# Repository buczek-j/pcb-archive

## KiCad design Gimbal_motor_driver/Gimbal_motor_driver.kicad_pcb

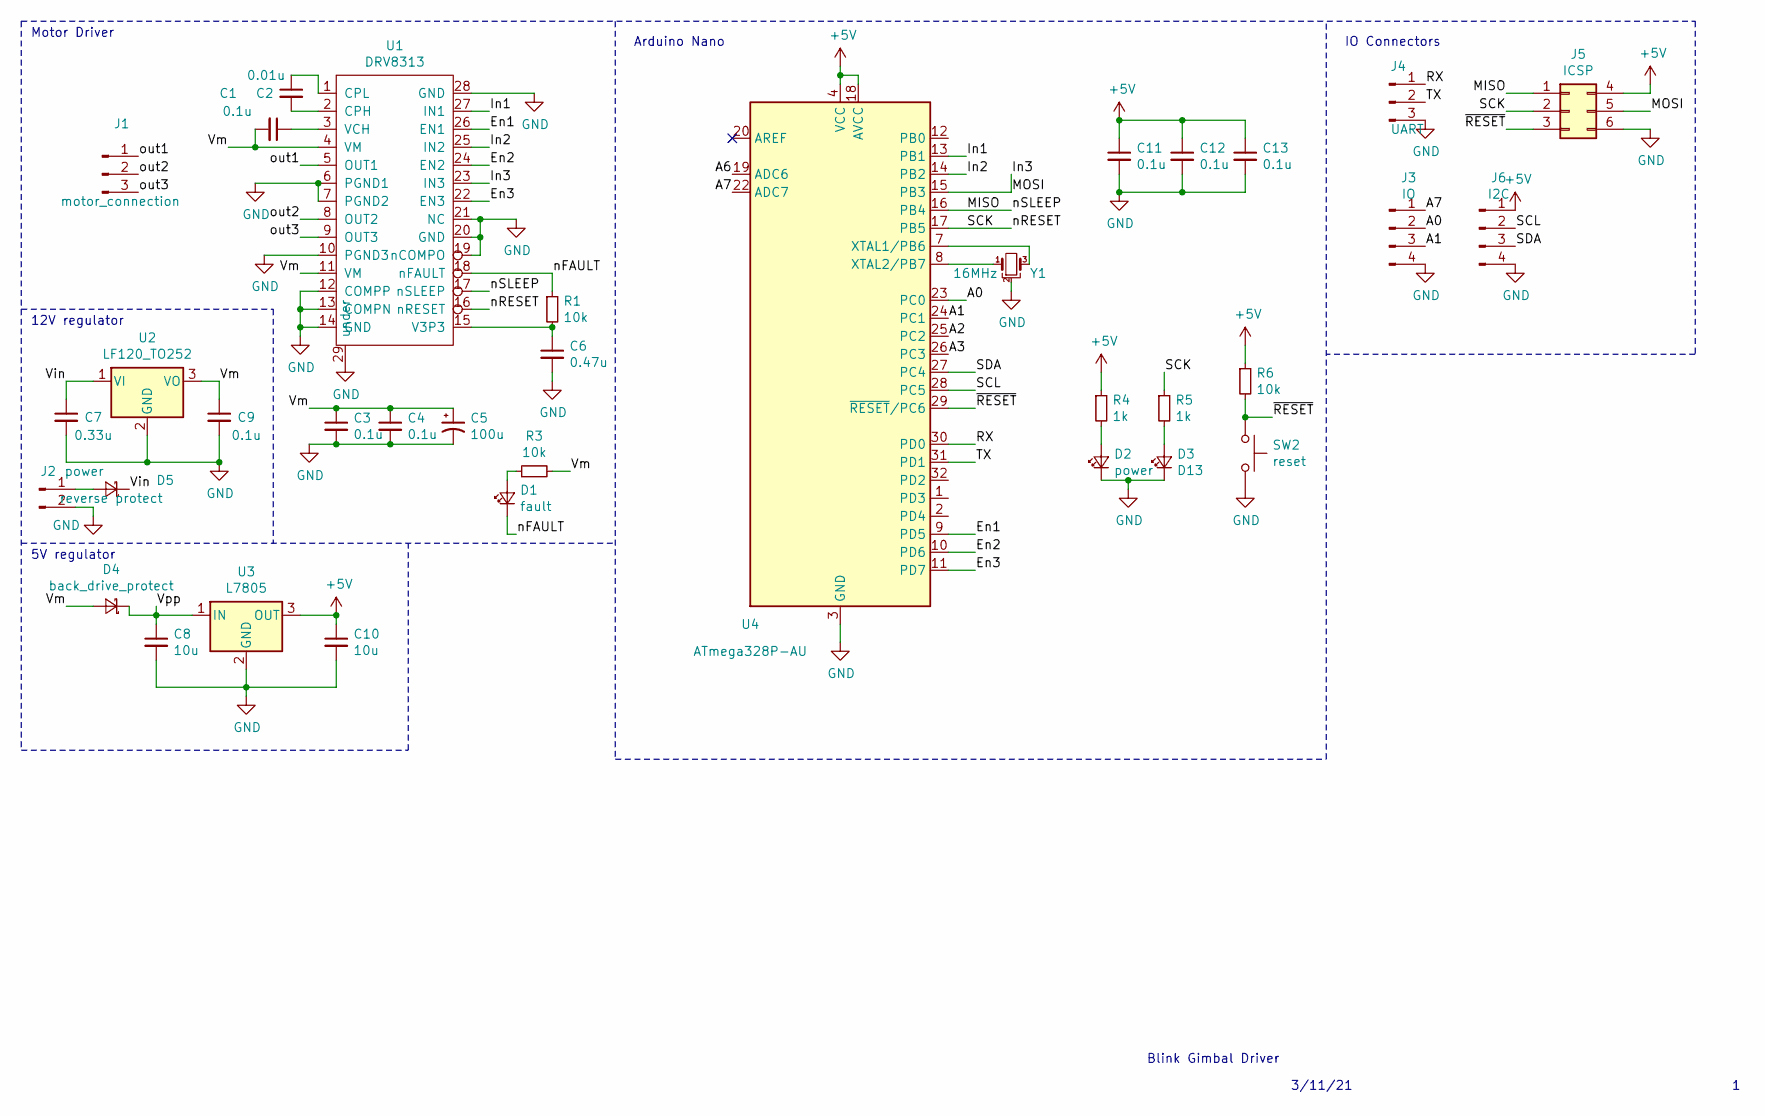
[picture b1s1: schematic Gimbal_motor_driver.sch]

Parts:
C1, C3, C4, C9, C11, C12, C13: 0.1u; C_0402_1005Metric
C2: 0.01u; C_0402_1005Metric
C5: 100u; C_1206_3216Metric_Pad1.42x1.75mm_HandSolder
C6: 0.47u; C_0402_1005Metric
C7: 0.33u; C_0402_1005Metric
C8, C10: 10u; C_0402_1005Metric
D1: fault; LED_0402_1005Metric
D2: power; LED_0402_1005Metric
D3: D13; LED_0402_1005Metric
D4: back_drive_protect; D_SOD-123
D5: reverse protect; D_SMB
J1: motor_connection; PinSocket_1x03_P2.54mm_Vertical
J2: power; PinHeader_1x02_P2.54mm_Vertical
J3: IO; PinHeader_1x04_P2.54mm_Vertical
J4: UART; PinSocket_1x03_P2.54mm_Vertical
J5: ICSP; PinHeader_2x03_P2.54mm_Vertical
J6: I2C; PinHeader_1x04_P2.54mm_Vertical
R1, R3, R6: 10k; R_0402_1005Metric
R4, R5: 1k; R_0402_1005Metric
SW2: reset; PinHeader_1x02_P1.27mm_Vertical
U1: DRV8313; HTSSOP-28-1EP_4.4x9.7mm_P0.65mm_EP2.85x5.4mm_ThermalVias
U2: LF120_TO252; TO-252-2
U3: L7805; SOT-223-3_TabPin2
U4: ATmega328P-AU; TQFP-32_7x7mm_P0.8mm
Y1: 16MHz; Resonator_SMD_muRata_CSTxExxV-3Pin_3.0x1.1mm

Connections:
+5V: C10.1, C11.1, C12.1, C13.1, J5.4, J6.1, R4.1, R6.1, U3.3 (OUT), U4.4 (VCC), U4.6 (VCC), U4.18 (AVCC)
/A0: J3.2, U4.23 (PC0)
/A1: J3.3, U4.24 (PC1)
/A2: U4.25 (PC2)
/A3: U4.26 (PC3)
/A6: U4.19 (ADC6)
/A7: J3.1, U4.22 (ADC7)
/En1: U1.26 (EN1), U4.9 (PD5)
/En2: U1.24 (EN2), U4.10 (PD6)
/En3: U1.22 (EN3), U4.11 (PD7)
/In1: U1.27 (IN1), U4.13 (PB1)
/In2: U1.25 (IN2), U4.14 (PB2)
/In3: J5.5, U1.23 (IN3), U4.15 (PB3)
/MISO: J5.1, U1.17 (nSLEEP), U4.16 (PB4)
/RX: J4.1, U4.30 (PD0)
/SCK: J5.2, R5.1, U1.16 (nRESET), U4.17 (PB5)
/SCL: J6.2, U4.28 (PC5)
/SDA: J6.3, U4.27 (PC4)
/TX: J4.2, U4.31 (PD1)
/Vin: C7.1, D5.1 (K), U2.1 (VI)
/Vm: C1.2, C3.1, C4.1, C5.1, C9.1, D4.2 (A), R3.2, U1.4 (VM), U1.11 (VM), U2.3 (VO)
/Vpp: C8.1, D4.1 (K), U3.1 (IN)
/nFAULT: D1.1 (K), R1.1, U1.18 (nFAULT)
/out1: J1.1, U1.5 (OUT1)
/out2: J1.2, U1.8 (OUT2)
/out3: J1.3, U1.9 (OUT3)
/~RESET: J5.3, R6.2, SW2.1, U4.29 (~RESET~/PC6)
GND: C3.2, C4.2, C5.2, C6.2, C7.2, C8.2, C9.2, C10.2, C11.2, C12.2, C13.2, D2.1 (K), D3.1 (K), J2.2, J3.4, J4.3, J5.6, J6.4, SW2.2, U1.6 (PGND1), U1.7 (PGND2), U1.10 (PGND3), U1.12 (COMPP), U1.13 (COMPN), U1.14 (GND), U1.19 (nCOMPO), U1.20 (GND), U1.21 (NC), U1.28 (GND), U1.29 (under), U2.2 (GND), U3.2 (GND), U4.3 (GND), U4.5 (GND), U4.21 (GND), Y1.2
unnamed: C1.1, U1.3 (VCH)
unnamed: C2.1, U1.1 (CPL)
unnamed: C2.2, U1.2 (CPH)
unnamed: C6.1, R1.2, U1.15 (V3P3)
unnamed: D1.2 (A), R3.1
unnamed: D2.2 (A), R4.2
unnamed: D3.2 (A), R5.2
unnamed: D5.2 (A), J2.1
unnamed: U4.7 (XTAL1/PB6), Y1.3
unnamed: U4.8 (XTAL2/PB7), Y1.1

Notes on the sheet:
Motor Driver
12V regulator
5V regulator
Arduino Nano
IO Connectors
Blink Gimbal Driver
3/11/21

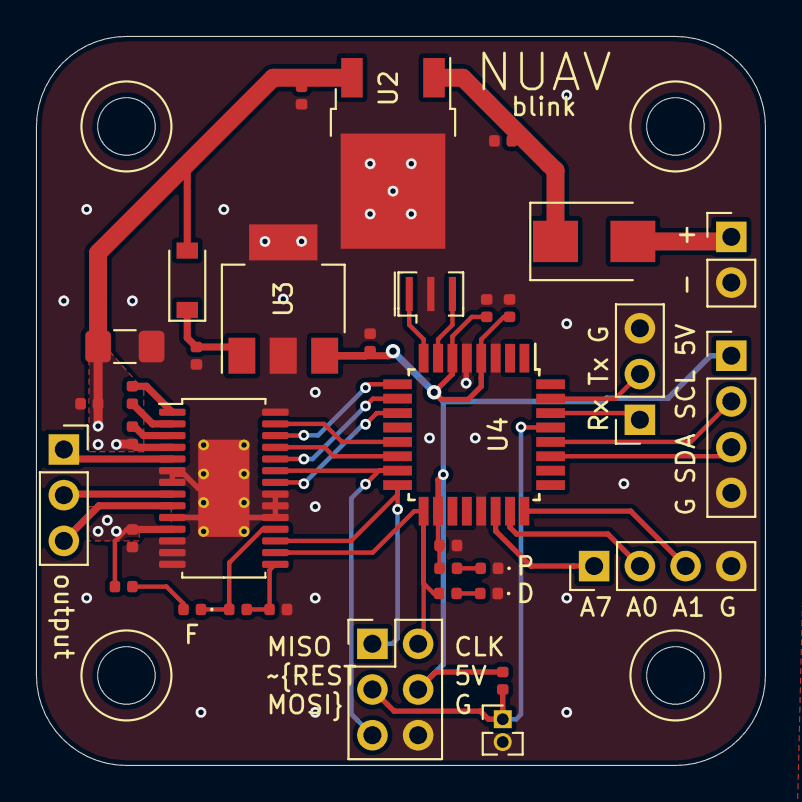
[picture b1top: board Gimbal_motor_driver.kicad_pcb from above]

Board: 2 copper layers, 40.5 x 40.5 mm, 35 parts (0 on the bottom side), 35 nets.

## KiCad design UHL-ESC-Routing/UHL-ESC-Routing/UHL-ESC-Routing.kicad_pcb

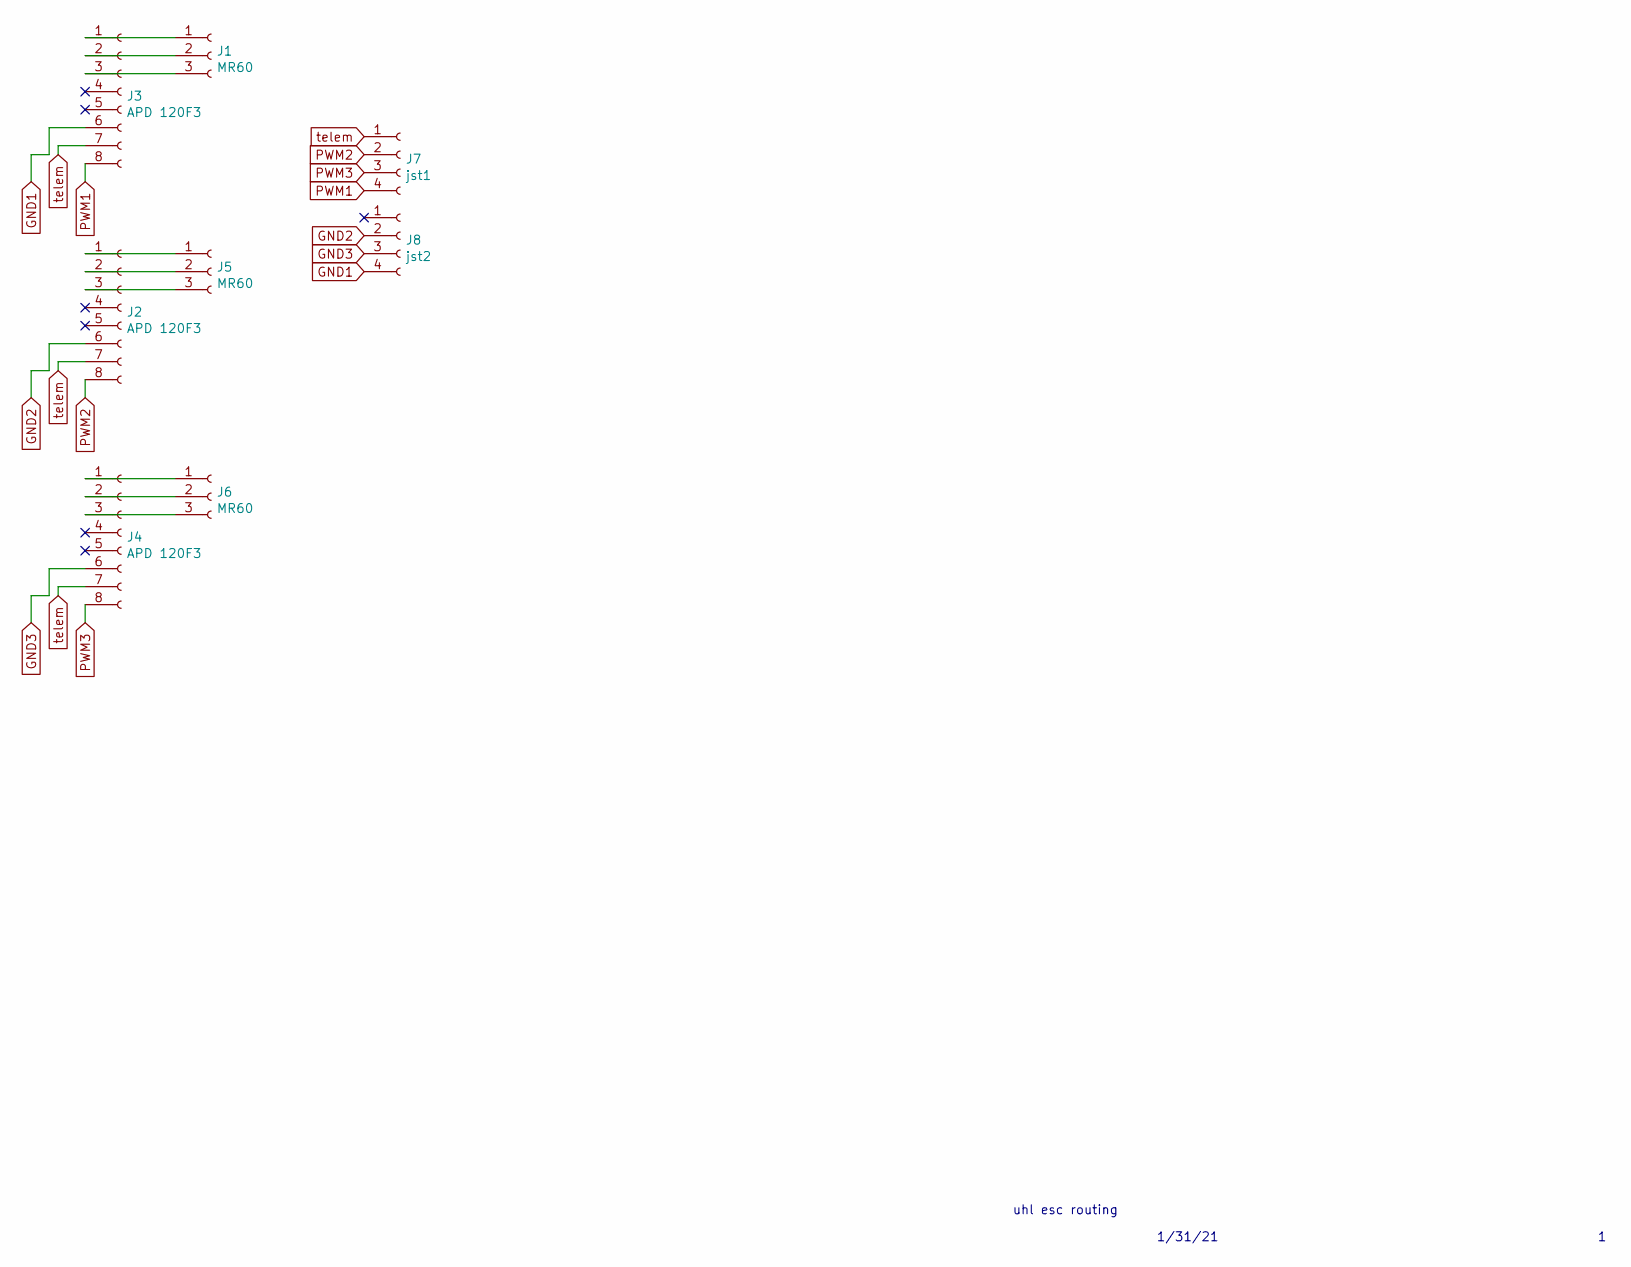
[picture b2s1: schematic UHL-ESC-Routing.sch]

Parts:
J1, J5, J6: MR60
J2, J3, J4: APD 120F3; APD-ESC
J7: jst1; PinHeader_1x04_P2.54mm_Vertical
J8: jst2; PinHeader_1x04_P2.54mm_Vertical

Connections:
GND1: J3.6, J8.4
GND2: J2.6, J8.2
GND3: J4.6, J8.3
unnamed: J1.1, J3.1
unnamed: J1.2, J3.2
unnamed: J1.3, J3.3
unnamed: J2.1, J5.1
unnamed: J2.2, J5.2
unnamed: J2.3, J5.3
unnamed: J4.1, J6.1
unnamed: J4.2, J6.2
unnamed: J4.3, J6.3
PWM1: J3.8, J7.4
PWM2: J2.8, J7.2
PWM3: J4.8, J7.3
telem: J2.7, J3.7, J4.7, J7.1

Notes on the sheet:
uhl esc routing
1/31/21

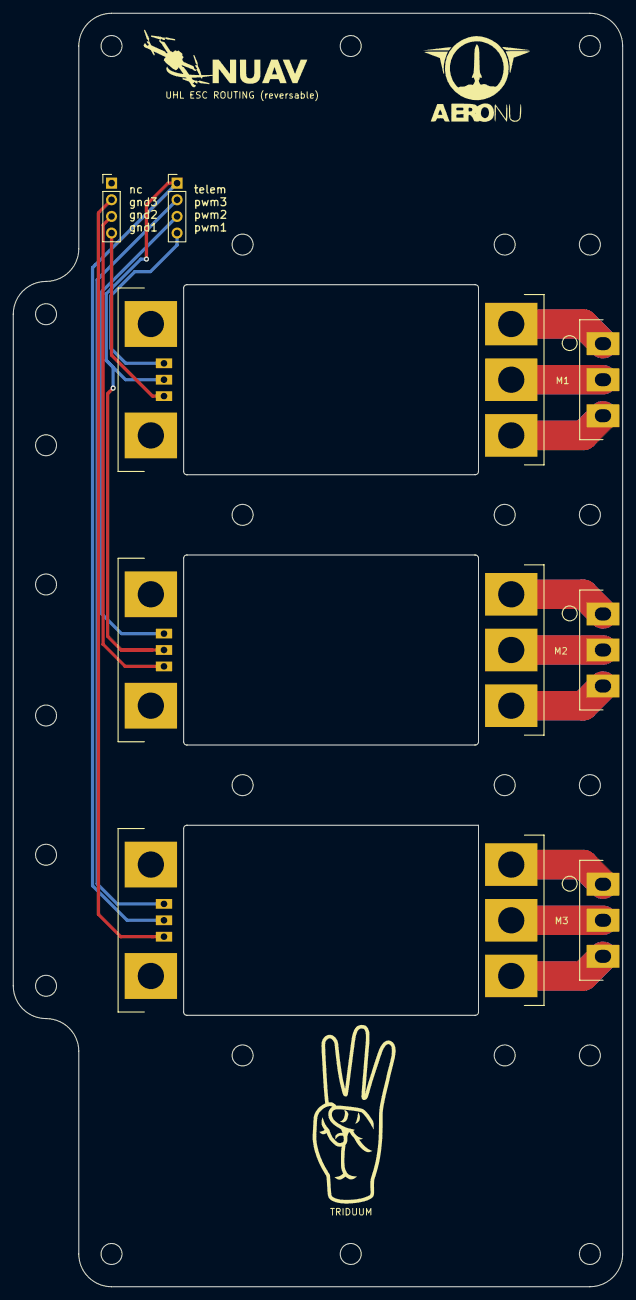
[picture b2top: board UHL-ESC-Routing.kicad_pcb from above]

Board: 2 copper layers, 93.0 x 194.4 mm, 8 parts (0 on the bottom side), 16 nets.

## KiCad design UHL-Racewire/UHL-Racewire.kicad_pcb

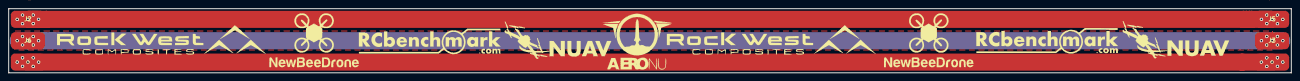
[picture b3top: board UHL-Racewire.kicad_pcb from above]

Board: 2 copper layers, 300.0 x 15.0 mm, 6 parts (0 on the bottom side), 3 nets.

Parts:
J1, J4: A; UHL-Racewire
J2, J5: B; UHL-Racewire
J3, J6: C; UHL-Racewire

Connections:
A: J1.1, J4.1
B: J2.1, J5.1
C: J3.1, J6.1

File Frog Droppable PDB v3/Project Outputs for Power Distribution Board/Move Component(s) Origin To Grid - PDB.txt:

Move Component(s) Origin to Grid
Filename     : P:\Ian User\Desktop\pcb-design\Frog Droppable PDB v3\PDB.PcbDoc
Date         : 5/25/2020
Time         : 9:33:08 PM
Time Elapsed : 00:00:00


    Small Component P4-TSW-103-08-T-S-RA (7667.323mil,1092.52mil) on Top Layer - Component origin is already ON grid. - Component pads are OFF grid. No action taken.
    Small Component P3-TSW-103-08-T-S-RA (2400mil,5462.598mil) on Top Layer - Component pads are OFF grid. No action taken.
    Small Component P2-TSW-103-08-T-S-RA (2610.081mil,952.911mil) on Top Layer - Component pads are OFF grid. No action taken.
    Small Component P1-TSW-103-08-T-S-RA (7537.795mil,5462.598mil) on Top Layer - Component pads are OFF grid. No action taken.
    Small Component J4-XT30PB-M (7411.417mil,482.284mil) on Top Layer - Component origin is already ON grid. - Component pads are OFF grid. No action taken.
    Small Component J3-XT30PB-M (1947.42mil,5579.31mil) on Top Layer - Component pads are OFF grid. No action taken.
    Small Component J2-XT30PB-M (2717.934mil,480.884mil) on Top Layer - Component pads are OFF grid. No action taken.
    Small Component J1-XT30PB-M (8200.218mil,5579.31mil) on Top Layer - Component pads are OFF grid. No action taken.
count : 8

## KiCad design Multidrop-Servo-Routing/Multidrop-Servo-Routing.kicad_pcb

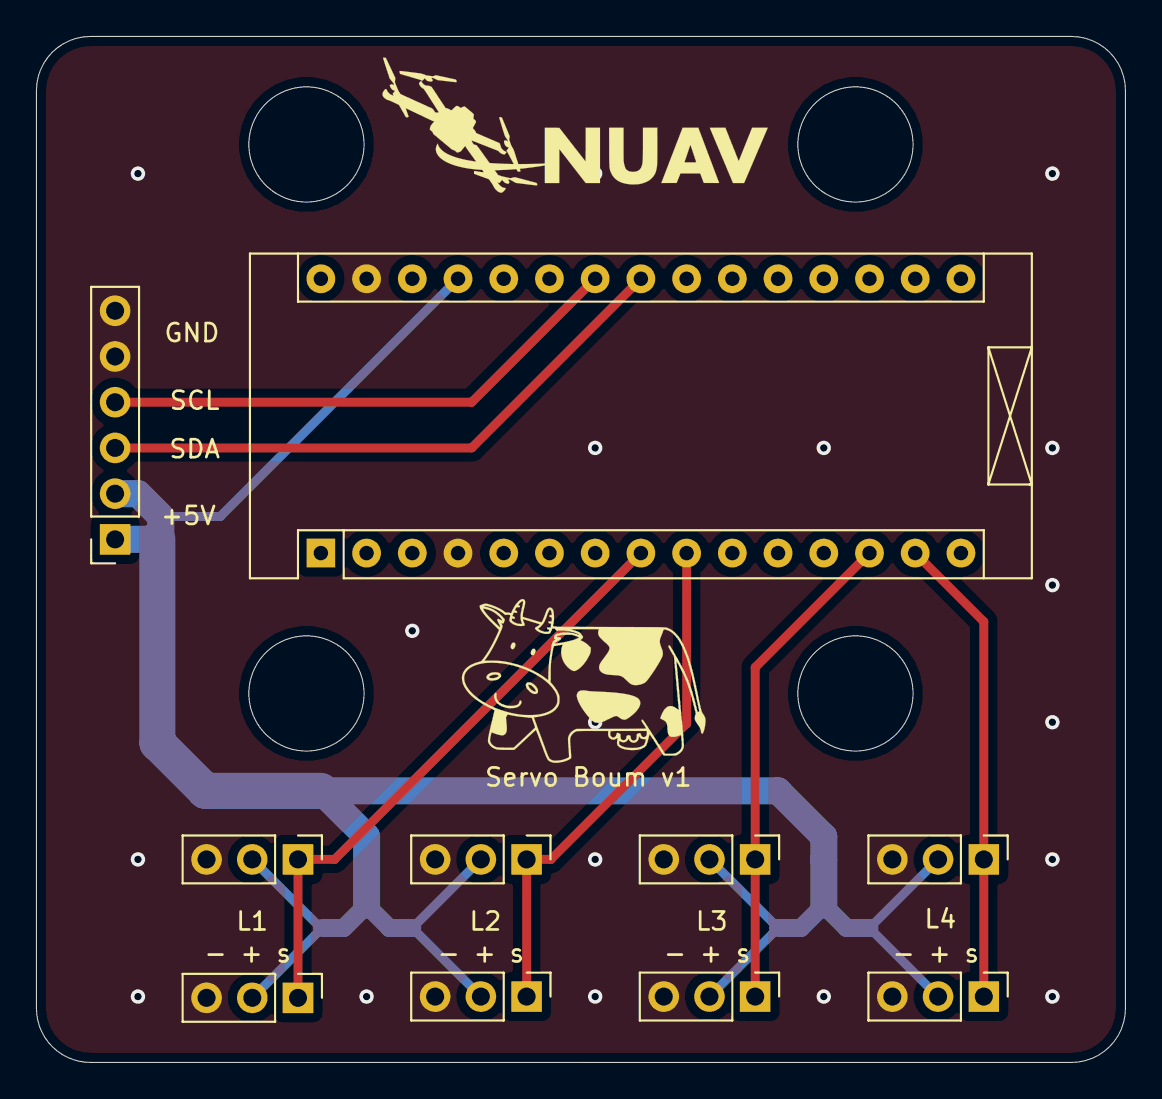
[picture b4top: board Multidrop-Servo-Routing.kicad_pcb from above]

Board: 2 copper layers, 60.5 x 57.0 mm, 10 parts (0 on the bottom side), 8 nets.

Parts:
A1: Arduino_Nano_v2.x; Arduino_Nano
J1, J2, J3, J4, J6, J7, J8, J9: Servo_Header; PinHeader_1x03_P2.54mm_Vertical
J5: Input_header; PinSocket_1x06_P2.54mm_Vertical

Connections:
+5V: A1.27, J1.2, J2.2, J3.2, J4.2, J5.1, J5.2, J6.2, J7.2, J8.2, J9.2
GND: A1.4, A1.29, J1.3, J2.3, J3.3, J4.3, J5.5, J5.6, J6.3, J7.3, J8.3, J9.3
SCL: A1.24, J5.4
SDA: A1.23, J5.3
Servo_1: A1.8, J1.1, J6.1
Servo_2: A1.9, J2.1, J7.1
Servo_3: A1.13, J3.1, J8.1
Servo_4: A1.14, J4.1, J9.1

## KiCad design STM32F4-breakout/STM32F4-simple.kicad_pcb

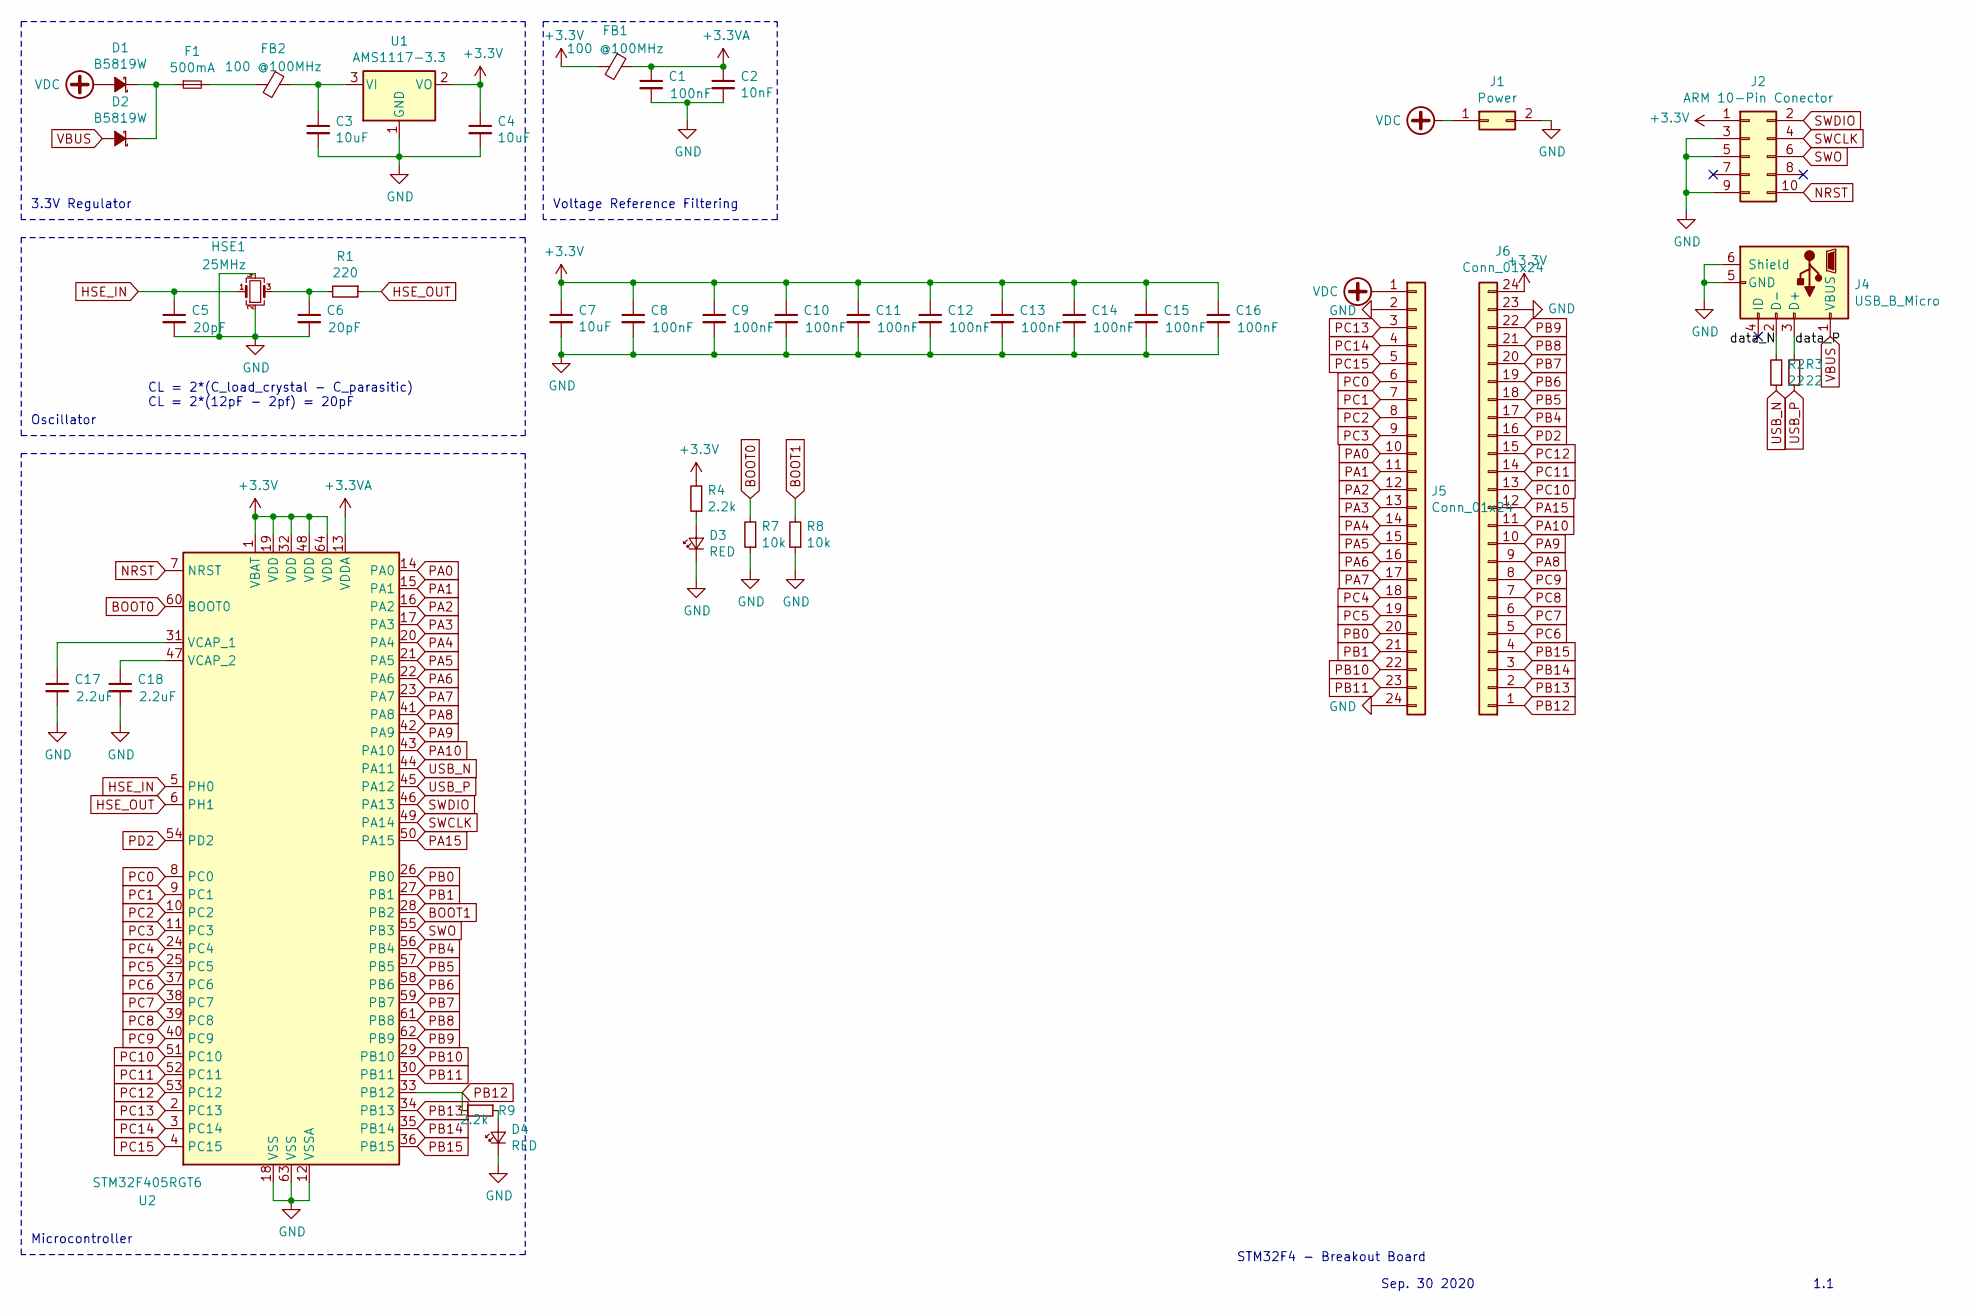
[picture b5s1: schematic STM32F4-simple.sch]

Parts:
C1, C8, C9, C10, C11, C12, C13, C14, C15, C16: 100nF; C_0402_1005Metric
C2: 10nF; C_0402_1005Metric
C3, C4, C7: 10uF; C_0402_1005Metric
C5, C6: 20pF; C_0402_1005Metric
C17, C18: 2.2uF; C_0402_1005Metric
D1, D2: B5819W; D_SOD-123
D3, D4: RED; D_0402_1005Metric
F1: 500mA; Fuse_0805_2012Metric
FB1, FB2: 100 @100MHz; L_0805_2012Metric
HSE1: 25MHz; Crystal_SMD_Abracon_ABM8G-4Pin_3.2x2.5mm
J1: Power; PinHeader_1x02_P2.54mm_Vertical
J2: ARM 10-Pin Conector; PinHeader_2x05_P1.27mm_Vertical_SMD
J4: USB_B_Micro; USB_Micro-B_Molex-105017-0001
J5, J6: Conn_01x24; PinHeader_1x24_P2.54mm_Vertical
R1: 220; R_0402_1005Metric
R2, R3: 22; R_0402_1005Metric
R4, R9: 2.2k; R_0402_1005Metric
R7, R8: 10k; R_0402_1005Metric
U1: AMS1117-3.3; SOT-223-3_TabPin2
U2: STM32F405RGT6; LQFP-64_10x10mm_P0.5mm

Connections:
+3.3VA: C1.1, C2.1, FB1.1, U2.13 (VDDA)
+3V3: C4.1, C7.1, C8.1, C9.1, C10.1, C11.1, C12.1, C13.1, C14.1, C15.1, C16.1, FB1.2, J2.1, J6.24, R4.2, U1.2 (VO), U2.1 (VBAT), U2.19 (VDD), U2.32 (VDD), U2.48 (VDD), U2.64 (VDD)
/data_N: J4.2 (D-), R2.2
/data_P: J4.3 (D+), R3.2
BOOT0: R7.2, U2.60 (BOOT0)
BOOT1: R8.2, U2.28 (PB2)
GND: C1.2, C2.2, C3.2, C4.2, C5.2, C6.2, C7.2, C8.2, C9.2, C10.2, C11.2, C12.2, C13.2, C14.2, C15.2, C16.2, C17.2, C18.2, D3.1 (K), D4.1 (K), HSE1.2, HSE1.4, J1.2, J2.3, J2.5, J2.9, J4.5 (GND), J4.6 (Shield), J5.2, J5.24, J6.23, R7.1, R8.1, U1.1 (GND), U2.12 (VSSA), U2.18 (VSS), U2.63 (VSS)
HSE_IN: C5.1, HSE1.1, U2.5 (PH0)
HSE_OUT: R1.1, U2.6 (PH1)
NRST: J2.10, U2.7 (NRST)
unnamed: C3.1, FB2.1, U1.3 (VI)
unnamed: C6.1, HSE1.3, R1.2
unnamed: C17.1, U2.31 (VCAP_1)
unnamed: C18.1, U2.47 (VCAP_2)
unnamed: D1.1 (K), D2.1 (K), F1.1
unnamed: D3.2 (A), R4.1
unnamed: D4.2 (A), R9.1
unnamed: F1.2, FB2.2
PA0: J5.10, U2.14 (PA0)
PA1: J5.11, U2.15 (PA1)
PA2: J5.12, U2.16 (PA2)
PA3: J5.13, U2.17 (PA3)
PA4: J5.14, U2.20 (PA4)
PA5: J5.15, U2.21 (PA5)
PA6: J5.16, U2.22 (PA6)
PA7: J5.17, U2.23 (PA7)
PA8: J6.9, U2.41 (PA8)
PA9: J6.10, U2.42 (PA9)
PA10: J6.11, U2.43 (PA10)
PA15: J6.12, U2.50 (PA15)
PB0: J5.20, U2.26 (PB0)
PB1: J5.21, U2.27 (PB1)
PB4: J6.17, U2.56 (PB4)
PB5: J6.18, U2.57 (PB5)
PB6: J6.19, U2.58 (PB6)
PB7: J6.20, U2.59 (PB7)
PB8: J6.21, U2.61 (PB8)
PB9: J6.22, U2.62 (PB9)
PB10: J5.22, U2.29 (PB10)
PB11: J5.23, U2.30 (PB11)
PB12: J6.1, R9.2, U2.33 (PB12)
PB13: J6.2, U2.34 (PB13)
PB14: J6.3, U2.35 (PB14)
PB15: J6.4, U2.36 (PB15)
PC0: J5.6, U2.8 (PC0)
PC1: J5.7, U2.9 (PC1)
PC2: J5.8, U2.10 (PC2)
PC3: J5.9, U2.11 (PC3)
PC4: J5.18, U2.24 (PC4)
PC5: J5.19, U2.25 (PC5)
PC6: J6.5, U2.37 (PC6)
PC7: J6.6, U2.38 (PC7)
PC8: J6.7, U2.39 (PC8)
PC9: J6.8, U2.40 (PC9)
PC10: J6.13, U2.51 (PC10)
PC11: J6.14, U2.52 (PC11)
PC12: J6.15, U2.53 (PC12)
PC13: J5.3, U2.2 (PC13)
PC14: J5.4, U2.3 (PC14)
PC15: J5.5, U2.4 (PC15)
PD2: J6.16, U2.54 (PD2)
SWCLK: J2.4, U2.49 (PA14)
SWDIO: J2.2, U2.46 (PA13)
SWO: J2.6, U2.55 (PB3)
USB_N: R2.1, U2.44 (PA11)
USB_P: R3.1, U2.45 (PA12)
VBUS: D2.2 (A), J4.1 (VBUS)
VDC: D1.2 (A), J1.1, J5.1

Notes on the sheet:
3.3V Regulator
Voltage Reference Filtering
CL = 2*(C_load_crystal - C_parasitic) CL = 2*(12pF - 2pf) = 20pF
Oscillator
Microcontroller
Sep. 30 2020
1.1
STM32F4 - Breakout Board

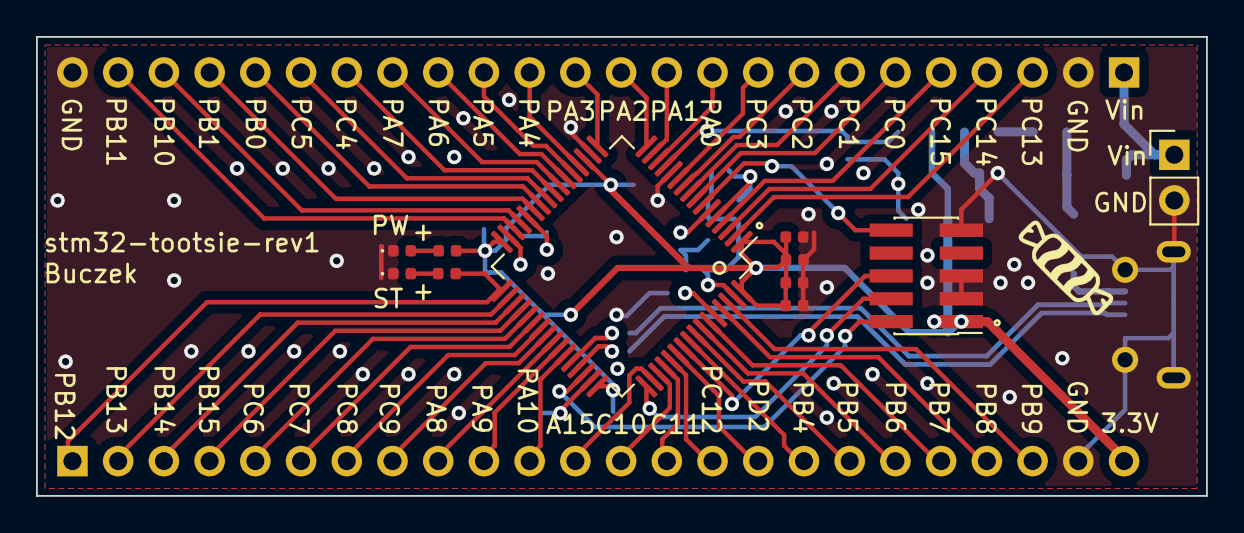
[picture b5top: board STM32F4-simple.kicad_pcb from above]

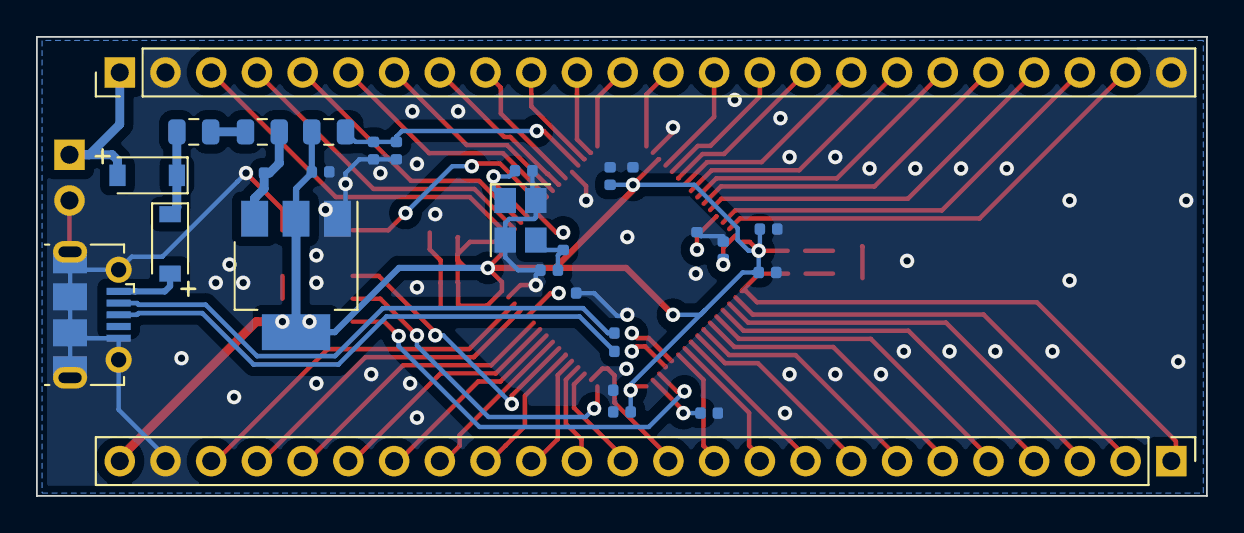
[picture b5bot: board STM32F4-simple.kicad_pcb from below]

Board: 4 copper layers, 65.0 x 25.5 mm, 40 parts (29 on the bottom side), 68 nets.

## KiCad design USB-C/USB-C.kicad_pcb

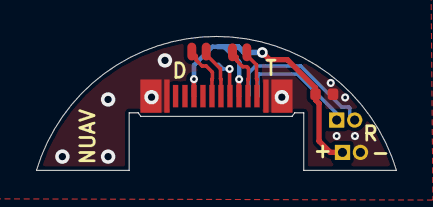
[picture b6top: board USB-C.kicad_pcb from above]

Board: 4 copper layers, 20.0 x 7.4 mm, 7 parts (1 on the bottom side), 9 nets.

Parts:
Cbp1: 10nF; C_0402_1005Metric
J1, J2: Conn_01x02; Pins-custom
J3, J4: Conn_01x02; PinHeader_1x02_P1.00mm_Vertical
Rp1: 56kR; R_0402_1005Metric
Ur: CX60-24S-UNIT

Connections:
D1_N: J1.1, Ur.A7
D1_P: J1.2, Ur.A6
GND: Cbp1.2, J4.2, Ur.A1, Ur.A12, Ur.B1, Ur.B12, Ur.Mount1, Ur.Mount2, Ur.Mount3, Ur.Mount4
RX1_N: J3.2, Ur.B10
RX1_P: J3.1, Ur.B11
Rp: Rp1.2, Ur.A5
TX1_N: J2.1, Ur.A3
TX1_P: J2.2, Ur.A2
VBUS: Cbp1.1, J4.1, Rp1.1, Ur.A4, Ur.A9, Ur.B4, Ur.B9

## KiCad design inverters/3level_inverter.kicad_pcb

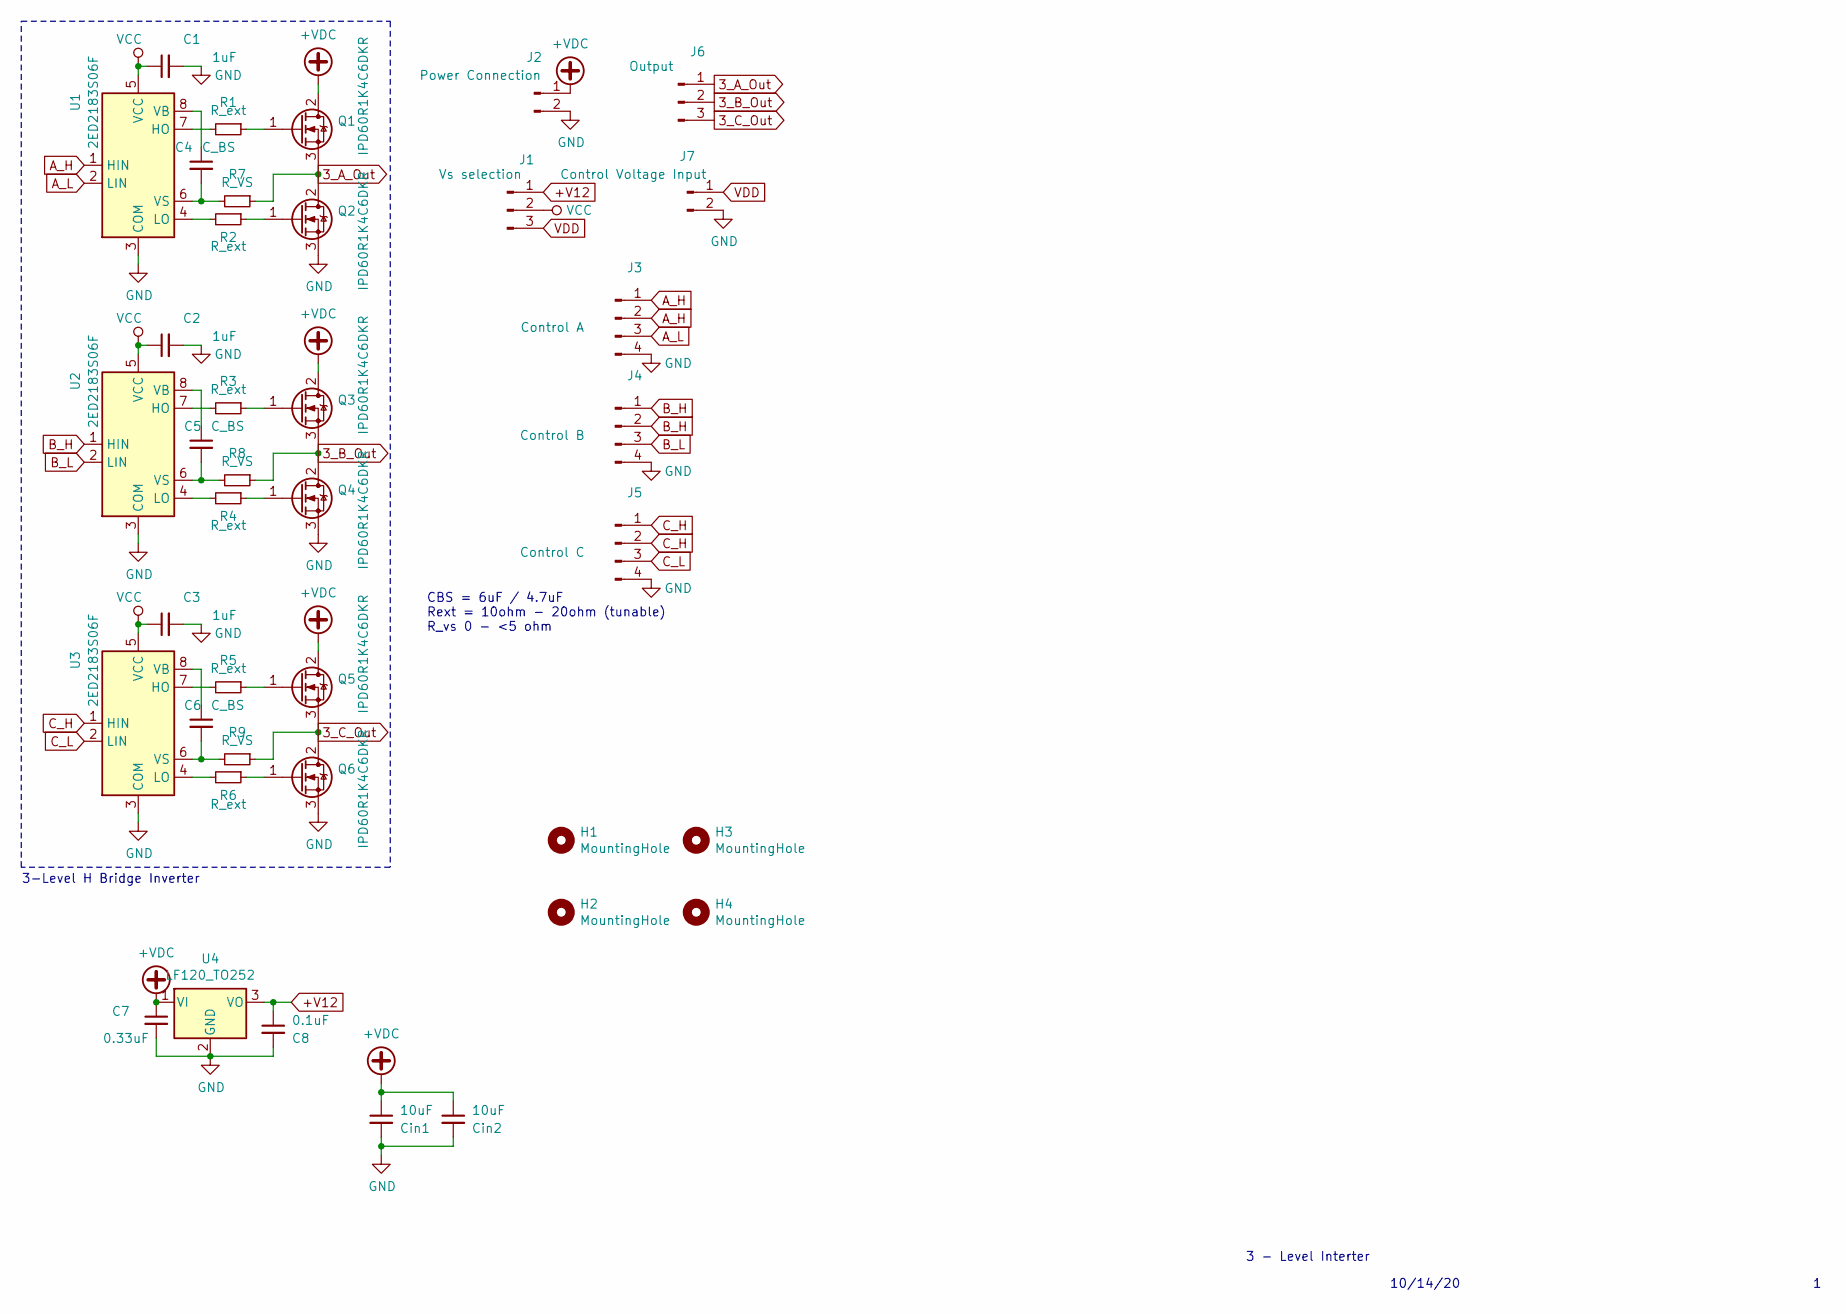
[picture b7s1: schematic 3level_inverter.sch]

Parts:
C1, C2, C3: 1uF; C_0805_2012Metric
C4, C5, C6: C_BS; C_0805_2012Metric
C7: 0.33uF; C_0603_1608Metric
C8: 0.1uF; C_0603_1608Metric
Cin1, Cin2: 10uF; C_2220_5650Metric
H1, H2, H3, H4: MountingHole; MountingHole_3.2mm_M3
J1: Vs selection; PinHeader_1x03_P2.54mm_Vertical
J2: Power Connection; SolderWirePad_1x02_P7.62mm_Drill2.5mm
J3: Control A; PinHeader_1x04_P2.54mm_Vertical
J4: Control B; PinHeader_1x04_P2.54mm_Vertical
J5: Control C; PinHeader_1x04_P2.54mm_Vertical
J6: Output; SolderWirePad_1x03_P4.445mm_Drill1.5mm
J7: Control Voltage Input; PinHeader_1x02_P2.54mm_Vertical
Q1, Q2, Q3, Q4, Q5, Q6: IPD60R1K4C6DKR; TO-252-2
R1, R2, R3, R4, R5, R6: R_ext; R_0603_1608Metric
R7, R8, R9: R_VS; R_0603_1608Metric
U1, U2, U3: 2ED2183S06F; SO-8_3.9x4.9mm_P1.27mm
U4: LF120_TO252; TO-252-2

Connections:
3_A_Out: J6.1, Q1.3 (S), Q2.2 (D), R7.1
3_B_Out: J6.2, Q3.3 (S), Q4.2 (D), R8.1
3_C_Out: J6.3, Q5.3 (S), Q6.2 (D), R9.1
+V12: C8.1, J1.1, U4.3 (VO)
+VDC: C7.1, Cin1.1, Cin2.1, J2.1, Q1.2 (D), Q3.2 (D), Q5.2 (D), U4.1 (VI)
A_H: J3.1, J3.2, U1.1 (HIN)
A_L: J3.3, U1.2 (LIN)
B_H: J4.1, J4.2, U2.1 (HIN)
B_L: J4.3, U2.2 (LIN)
C_H: J5.1, J5.2, U3.1 (HIN)
C_L: J5.3, U3.2 (LIN)
GND: C1.2, C2.2, C3.2, C7.2, C8.2, Cin1.2, Cin2.2, J2.2, J3.4, J4.4, J5.4, J7.2, Q2.3 (S), Q4.3 (S), Q6.3 (S), U1.3 (COM), U2.3 (COM), U3.3 (COM), U4.2 (GND)
unnamed: C4.1, U1.8 (VB)
unnamed: C4.2, R7.2, U1.6 (VS)
unnamed: C5.1, U2.8 (VB)
unnamed: C5.2, R8.2, U2.6 (VS)
unnamed: C6.1, U3.8 (VB)
unnamed: C6.2, R9.2, U3.6 (VS)
unnamed: Q1.1 (G), R1.1
unnamed: Q2.1 (G), R2.1
unnamed: Q3.1 (G), R3.1
unnamed: Q4.1 (G), R4.1
unnamed: Q5.1 (G), R5.1
unnamed: Q6.1 (G), R6.1
unnamed: R1.2, U1.7 (HO)
unnamed: R2.2, U1.4 (LO)
unnamed: R3.2, U2.7 (HO)
unnamed: R4.2, U2.4 (LO)
unnamed: R5.2, U3.7 (HO)
unnamed: R6.2, U3.4 (LO)
VCC: C1.1, C2.1, C3.1, J1.2, U1.5 (VCC), U2.5 (VCC), U3.5 (VCC)
VDD: J1.3, J7.1

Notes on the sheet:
3-Level H Bridge Inverter
CBS = 6uF / 4.7uF Rext = 10ohm - 20ohm (tunable) R_vs 0 - <5 ohm
3 - Level Interter
10/14/20

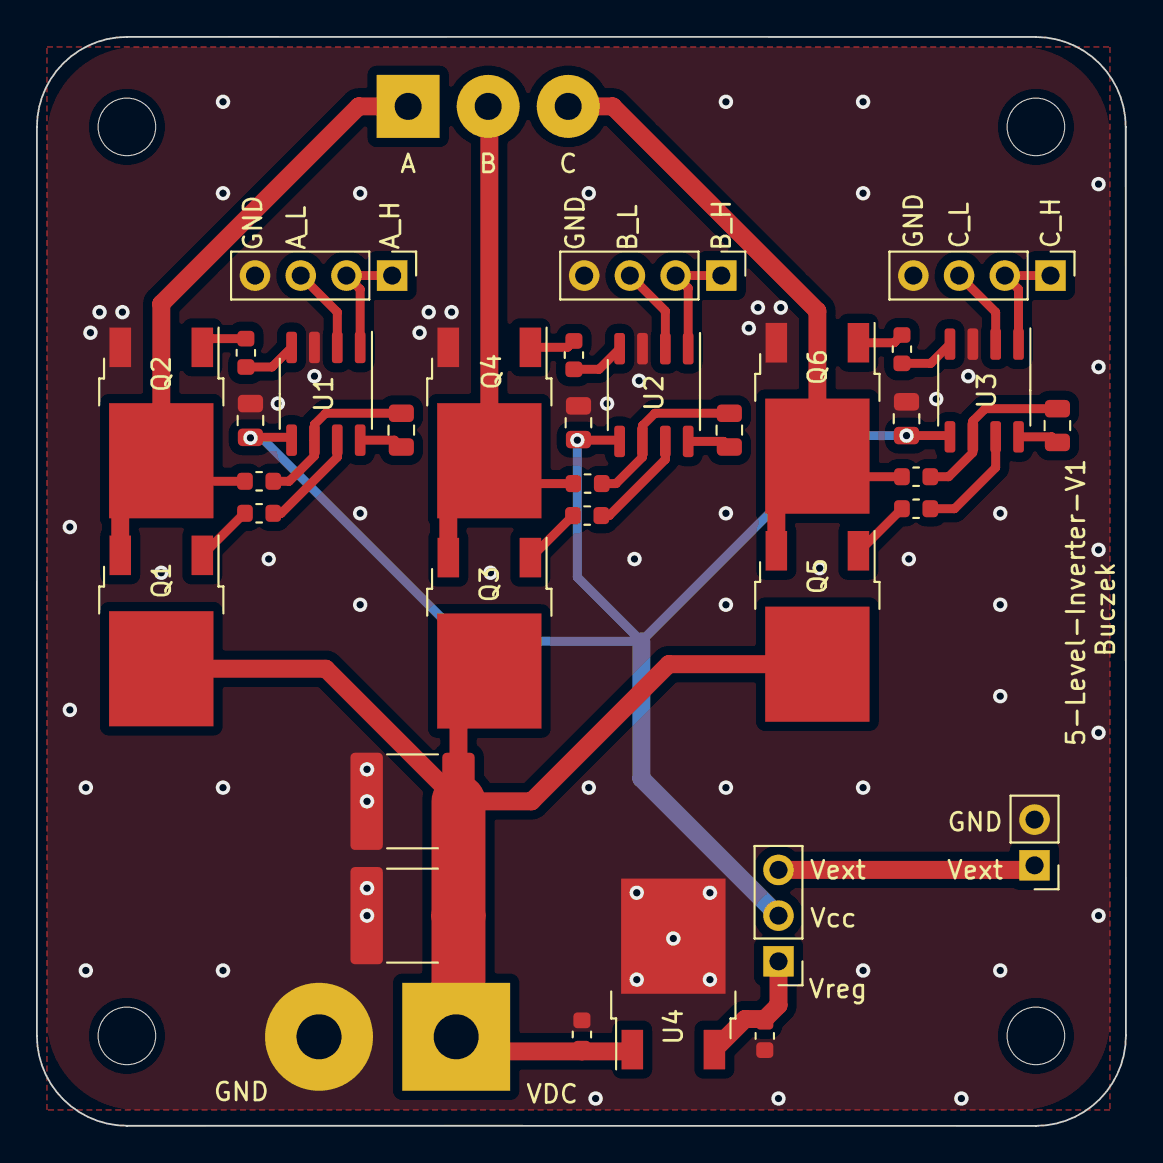
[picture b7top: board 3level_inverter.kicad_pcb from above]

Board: 2 copper layers, 60.5 x 60.5 mm, 40 parts (0 on the bottom side), 32 nets.

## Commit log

2021-01-05 End of semester push
2021-01-18 created servo wire router
2021-02-21 UHL routing additions
2021-03-12 added brushless gimbal driver
